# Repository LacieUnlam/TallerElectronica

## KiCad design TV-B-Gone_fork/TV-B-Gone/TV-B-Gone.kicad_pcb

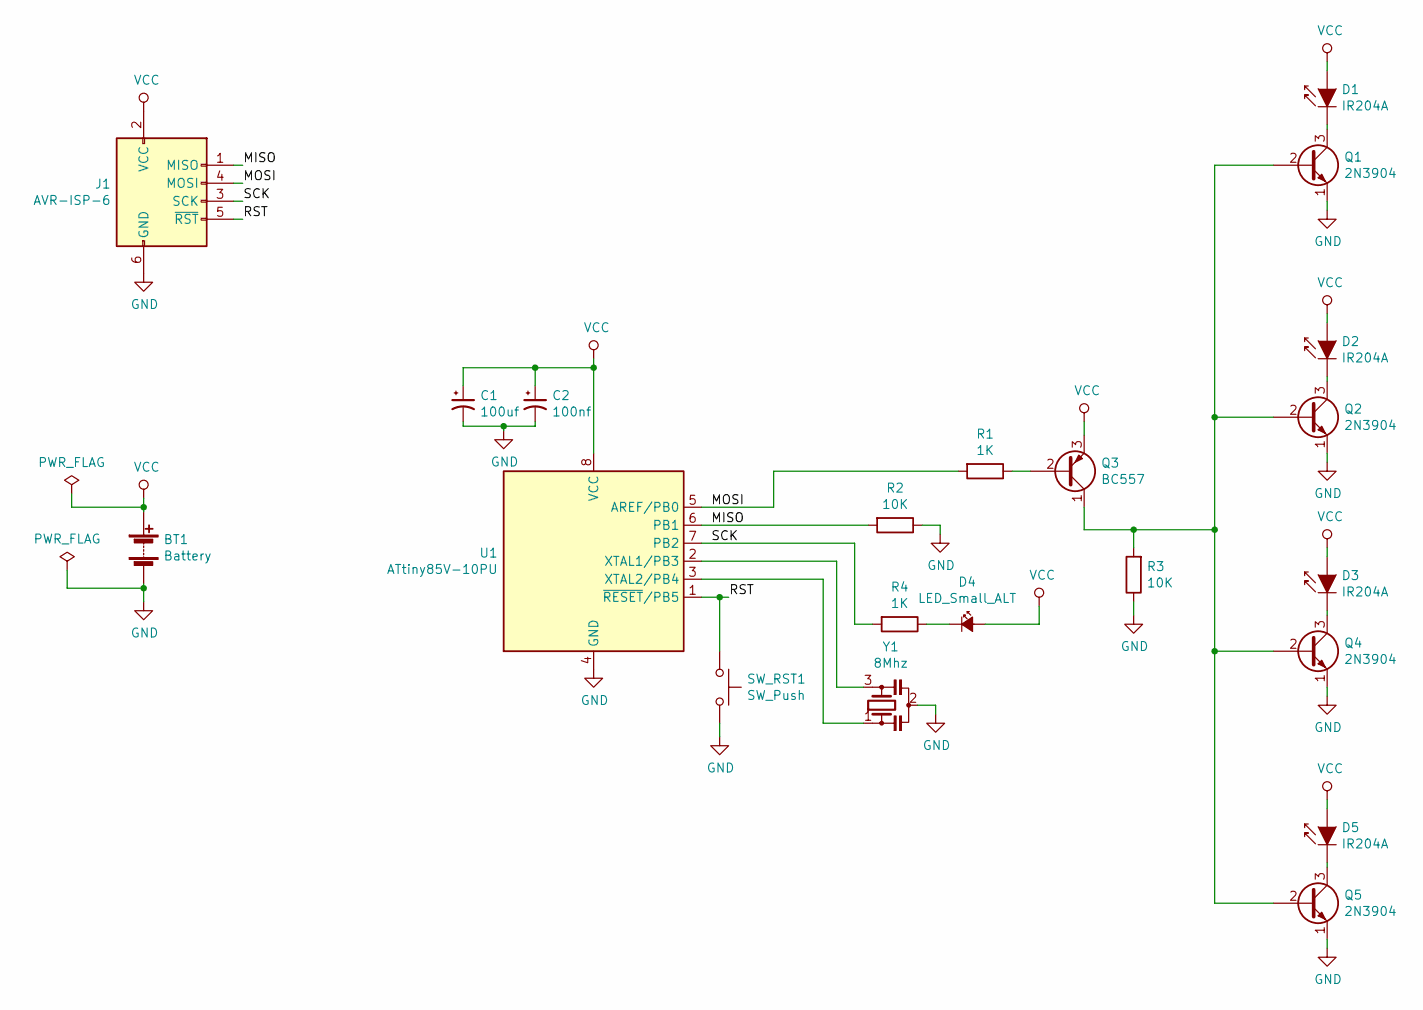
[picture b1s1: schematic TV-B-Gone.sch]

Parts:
BT1: Battery; PinHeader_1x02_P2.54mm_Vertical
C1: 100uf; CP_Radial_D6.3mm_P2.50mm
C2: 100nf; C_Disc_D6.0mm_W2.5mm_P5.00mm
D1, D2, D3, D5: IR204A; LED_D3.0mm_IRBlack
D4: LED_Small_ALT; LED_D3.0mm
J1: AVR-ISP-6; PinHeader_2x03_P2.54mm_Vertical
Q1, Q2, Q4, Q5: 2N3904; TO-92_Inline
Q3: BC557; TO-92_Inline
R1, R4: 1K; R_Axial_DIN0309_L9.0mm_D3.2mm_P12.70mm_Horizontal
R2, R3: 10K; R_Axial_DIN0309_L9.0mm_D3.2mm_P12.70mm_Horizontal
SW_RST1: SW_Push; SW_PUSH_6mm_H5mm
U1: ATtiny85V-10PU; DIP-8_W7.62mm
Y1: 8Mhz; Resonator-3Pin_W10.0mm_H5.0mm

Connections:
/MISO: J1.1 (MISO), R2.2, U1.6 (PB1)
/MOSI: J1.4 (MOSI), R1.2, U1.5 (AREF/PB0)
/RST: J1.5 (~RST), SW_RST1.1, U1.1 (~RESET~/PB5)
/SCK: J1.3 (SCK), R4.2, U1.7 (PB2)
GND: BT1.2 (-), C1.2, C2.2, J1.6 (GND), Q1.1 (E), Q2.1 (E), Q4.1 (E), Q5.1 (E), R2.1, R3.1, SW_RST1.2, U1.4 (GND), Y1.2; also elsewhere on the board
unnamed 5: U1.2 (XTAL1/PB3), Y1.3; also elsewhere on the board
unnamed 6: U1.3 (XTAL2/PB4), Y1.1; also elsewhere on the board
unnamed: D1.1 (K), Q1.3 (C)
unnamed: D2.1 (K), Q2.3 (C)
unnamed: D3.1 (K), Q4.3 (C)
unnamed: D4.1 (K), R4.1
unnamed: D5.1 (K), Q5.3 (C)
unnamed: Q1.2 (B), Q2.2 (B), Q3.1 (C), Q4.2 (B), Q5.2 (B), R3.2
unnamed: Q3.2 (B), R1.1
VCC: BT1.1 (+), C1.1, C2.1, D1.2 (A), D2.2 (A), D3.2 (A), D4.2 (A), D5.2 (A), J1.2 (VCC), Q3.3 (E), U1.8 (VCC)

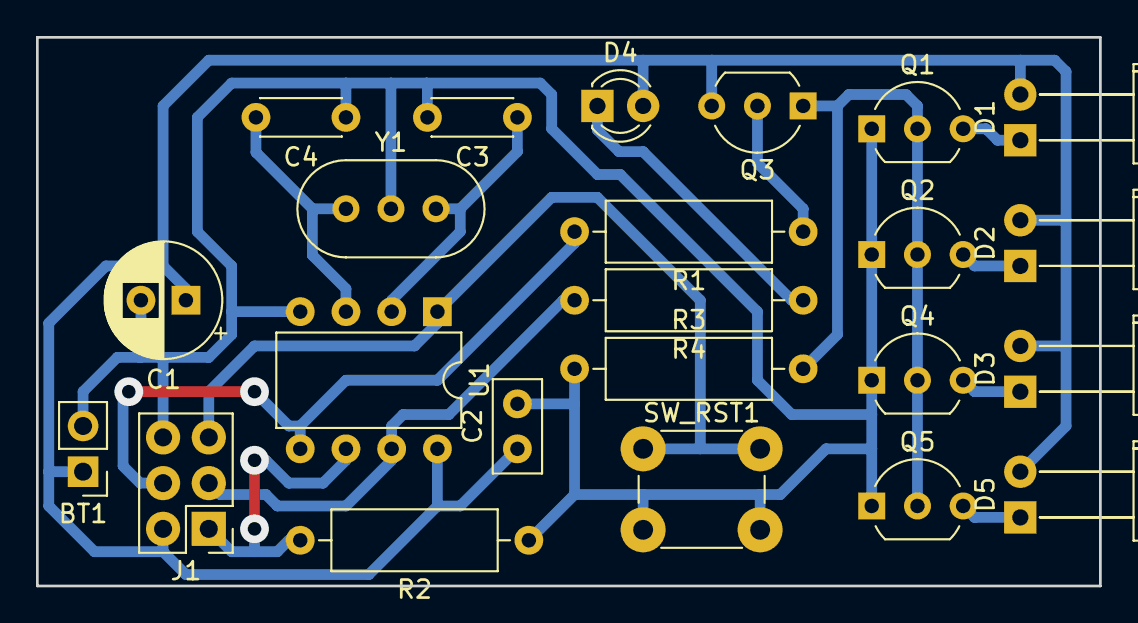
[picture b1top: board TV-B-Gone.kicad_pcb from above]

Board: 2 copper layers, 59.1 x 30.5 mm, 23 parts (0 on the bottom side), 15 nets.

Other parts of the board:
C3, C4: 18pf; C_Disc_D4.3mm_W1.9mm_P5.00mm

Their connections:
GND: C3.2, C4.1; also elsewhere on the board
unnamed 5: C3.1; also elsewhere on the board
unnamed 6: C4.2; also elsewhere on the board

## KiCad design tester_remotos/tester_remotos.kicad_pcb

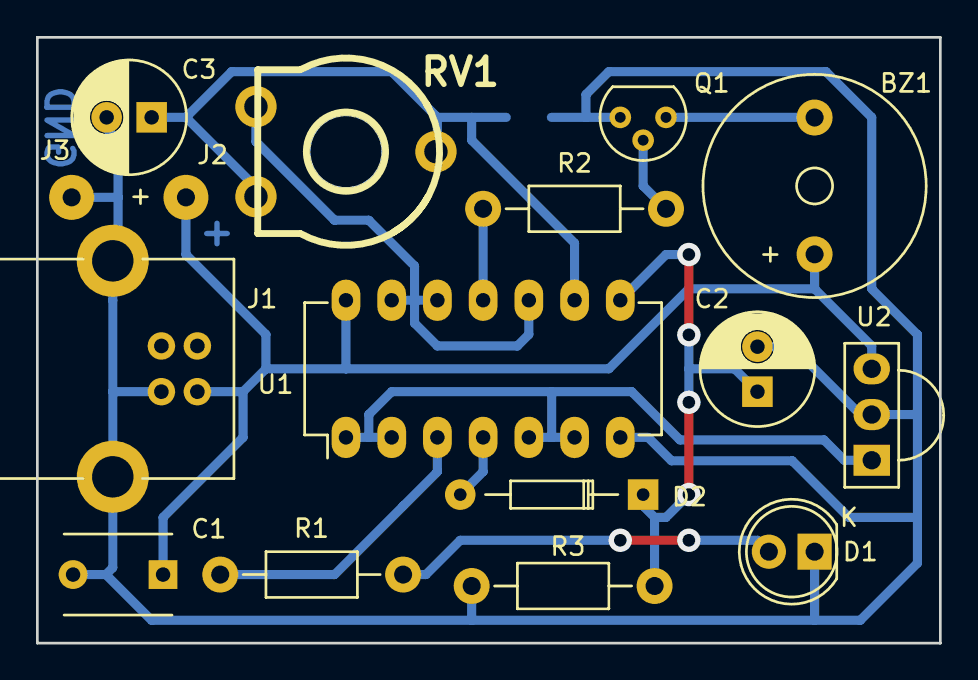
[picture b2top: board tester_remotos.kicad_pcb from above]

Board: 2 copper layers, 50.2 x 33.7 mm, 17 parts (1 on the bottom side), 12 nets.

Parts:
BZ1: Buzzer; Buzzer_12x9.5RM7.6
C1: 100nf; C_Disc_D6_P5
C2: 10 uF; C_Radial_D6.3_L11.2_P2.5
C3: 1 uF; C_Radial_D6.3_L11.2_P2.5
C4: 100nf; C_0805_HandSoldering
D1: LED; LED-5MM
D2: 1N4148; Diode_DO-35_SOD27_Horizontal_RM10
J1: USB_B
J2, J3: CONN_01X01; SolderWirePad_single_1mmDrill
Q1: BC548; TO-92_Molded_Narrow
R1: 1K; Resistor_Horizontal_RM10mm
R2: 1k; Resistor_Horizontal_RM10mm
R3: 4K7; Resistor_Horizontal_RM10mm
RV1: POT_TRIM; trimmer_piher_pt10xv10
U1: 4093; DIP-14_W7.62mm_LongPads
U2: VS1838B

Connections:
+5V: BZ1.1, C1.1, J1.1, J2.1, U1.14, U2.3
GND: C1.2, C2.2, C3.2, C4.2, D1.1, J1.4, J1.5, J3.1, Q1.3, R3.2, U1.7, U2.2
unnamed: BZ1.2, Q1.1
unnamed: C2.1, D2.1, R3.1, U1.8
unnamed: C3.1, C4.1, RV1.2, RV1.3, U1.9
unnamed: D1.2, R1.1
unnamed: D2.2, U1.4
unnamed: Q1.2, R2.1
unnamed: R1.2, U1.3
unnamed: R2.2, U1.11
unnamed: RV1.1, U1.10, U1.12, U1.13
unnamed: U1.1, U1.2, U1.5, U1.6, U2.1

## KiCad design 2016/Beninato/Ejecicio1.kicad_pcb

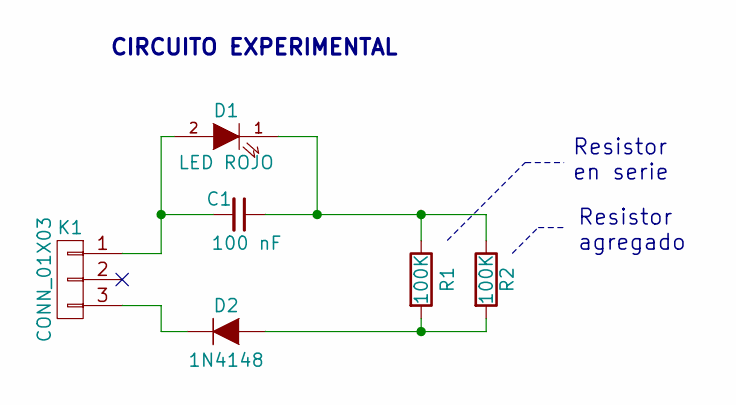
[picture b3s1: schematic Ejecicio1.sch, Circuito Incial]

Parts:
C1: 100 nF; C_Rect_L7_W3.5_P5
D1: LED ROJO; LED-3MM
D2: 1N4148; Diode_DO-35_SOD27_Horizontal_RM10
K1: CONN_01X03; bornier3
R1, R2: 100K; R3-LARGE_PADS

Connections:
unnamed: C1.1, D1.1 (K), R1.1, R2.1
unnamed: C1.2, D1.2 (A), K1.1
unnamed: D2.1 (K), K1.3
unnamed: D2.2 (A), R1.2, R2.2

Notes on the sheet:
Resistor en serie
CIRCUITO EXPERIMENTAL
Resistor agregado

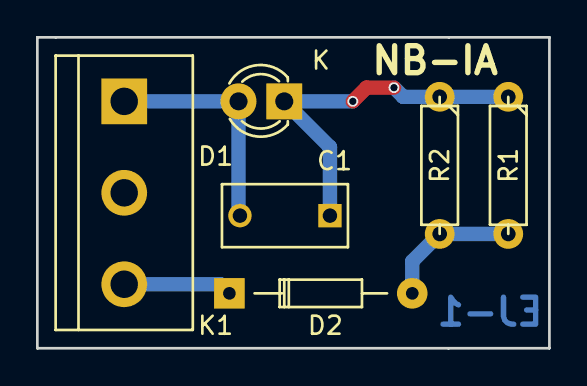
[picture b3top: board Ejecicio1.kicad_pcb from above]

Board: 2 copper layers, 28.4 x 17.3 mm, 6 parts (0 on the bottom side), 4 nets.

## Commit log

2018-05-10 Agregado circuito tester de control remoto infrarrojo.
2018-05-12 Módulo "probador de control remoto" terminado.
2018-05-14 Modificado de pads de varios footprints. Correción de algunos textos en esquemático.
2019-10-05 Mejoro clearance a 0,5 mm y actualizo a KiCad 5.1.
2019-10-05 Primer ingreso del proyecto TV-B-Gone_fork
2019-10-05 Agregado capacitores para optar entre resonador o cristal.
2019-10-07 Agregado libreria externa para algunos capacitores.
2019-10-08 Ruteando. Asignación modelo 3D capacitor.
2019-10-08 Ruteado terminado. Agregado de copia del software para la versión de hard.
2019-10-09 Agrandado de vias. Ajustes a clearance de 0.6 mm.
2019-10-10 Ajuste de vias a 1.6 mm, taladro 0.75 mm. Cambio de huella de algunos capacitores. Ajuste tamaño de pads algunos componentes. Eliminación de librerias de 3ros.
2019-10-17 Cambio huellas resistencias y ajuste de pistas.
2019-10-24 Archivado en la carpeta "orig" de los firmware originales del sitio web. Modificaciones al código según el post del foro adafruit "TV B GONE Not working after reprogramming (attiny)" (https://forums.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
